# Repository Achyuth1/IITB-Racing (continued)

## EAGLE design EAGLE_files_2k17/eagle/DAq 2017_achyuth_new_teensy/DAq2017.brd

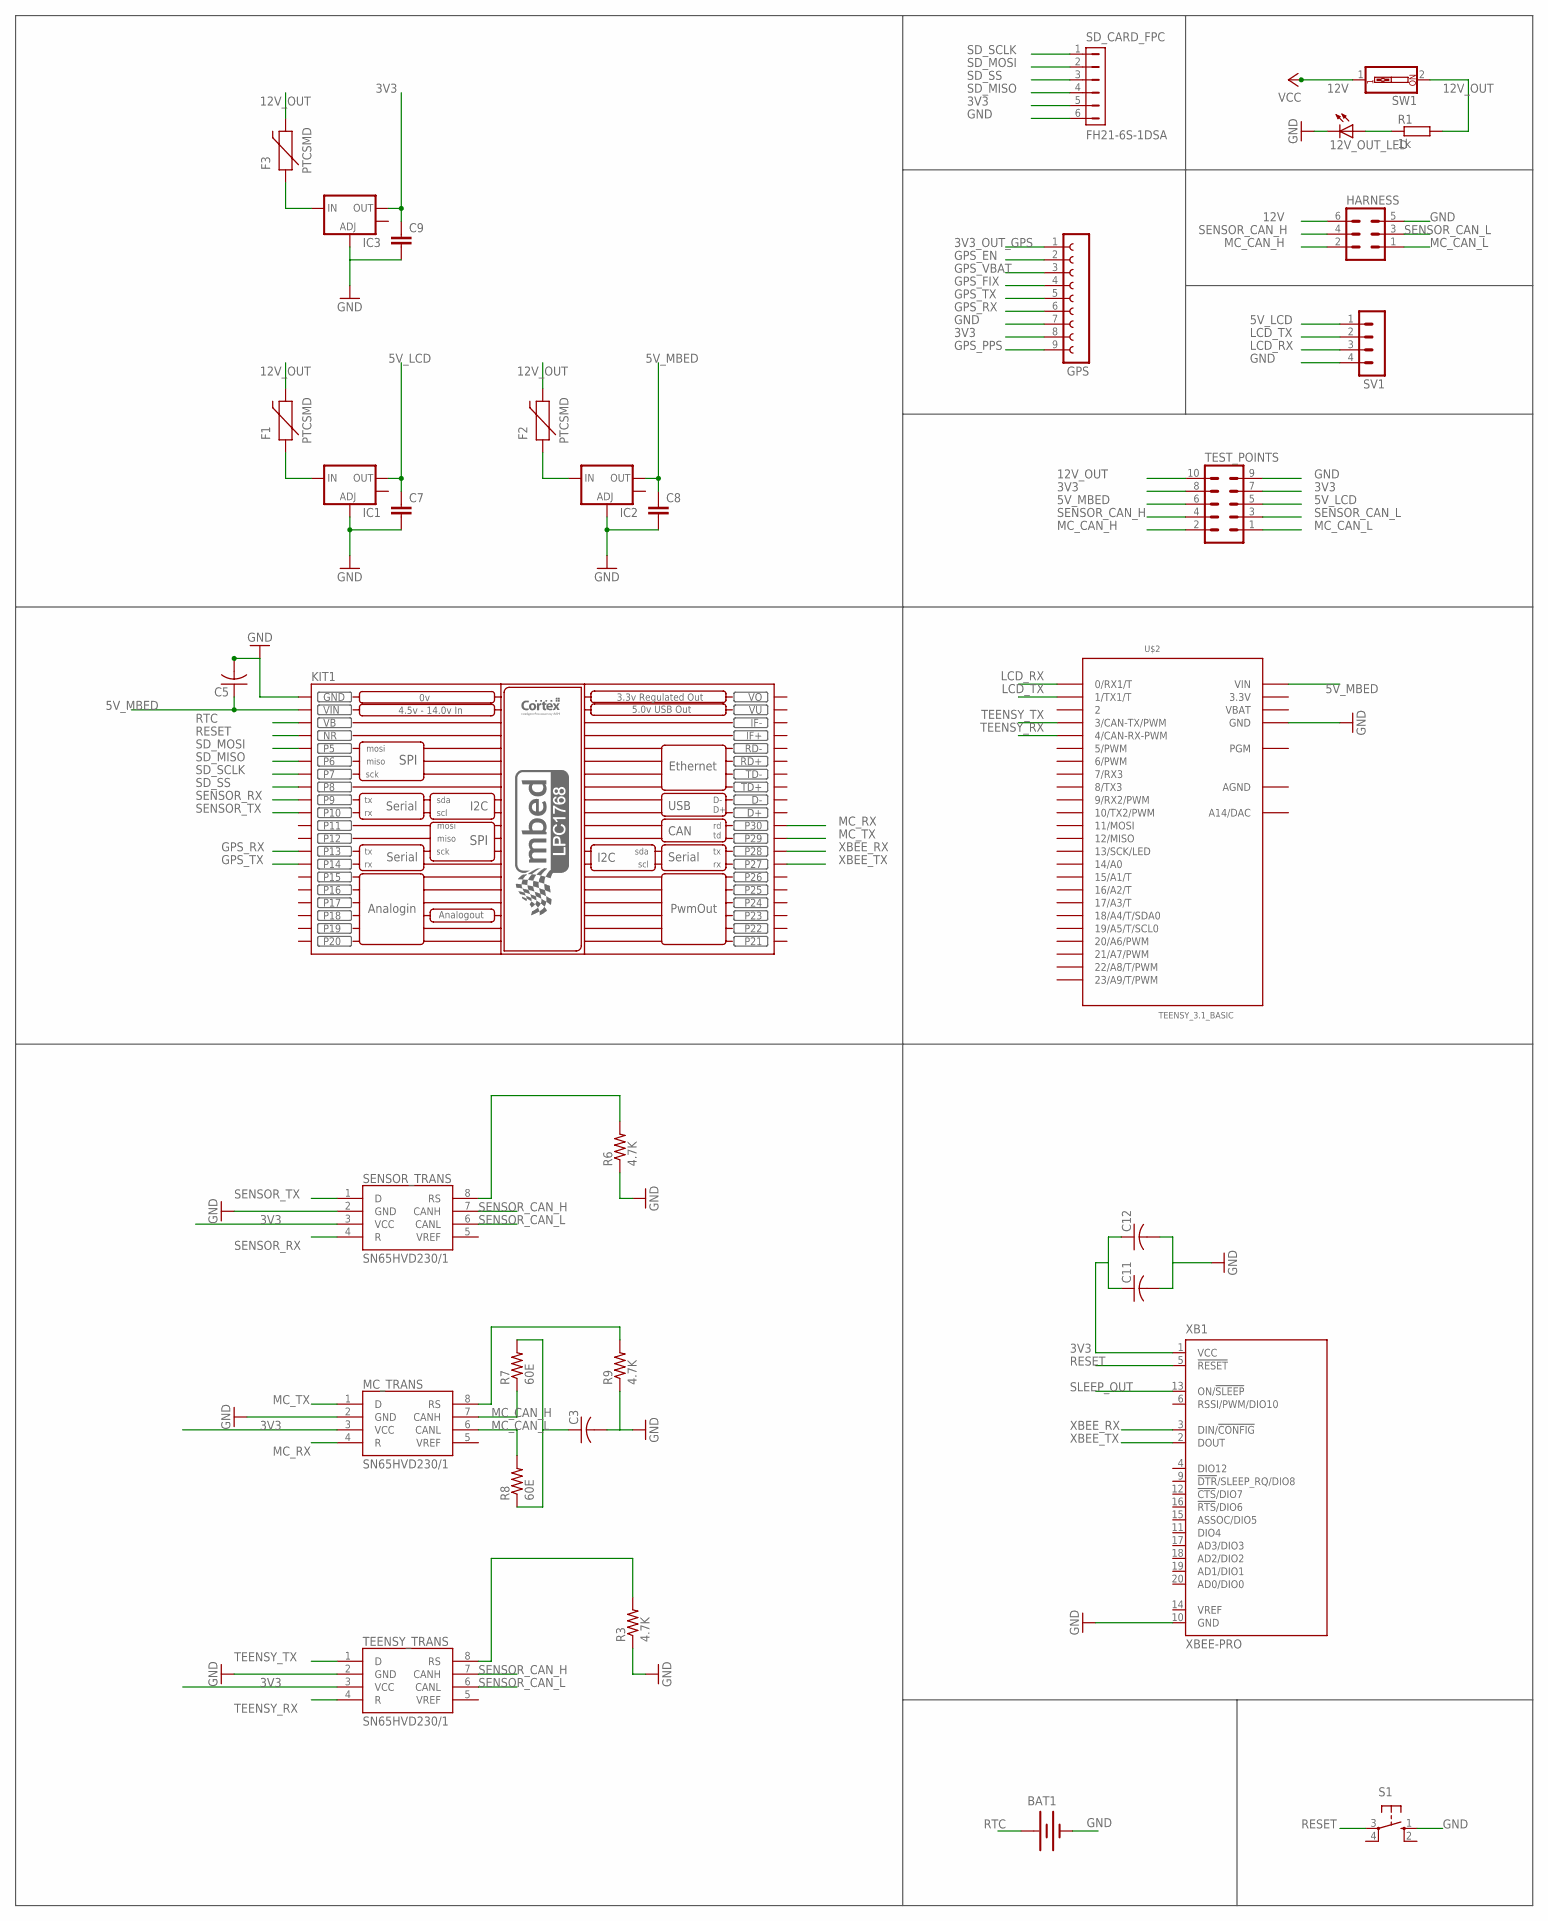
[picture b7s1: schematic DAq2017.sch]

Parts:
12V_OUT_LED: LEDCHIPLED_1206; CHIPLED_1206
BAT1: BATTERY20PTH; BATTCOM_20MM_PTH
C3, C5, C11, C12: C-USC0805; C0805
C7, C8, C9: C-EUC0805; C0805
F1, F2, F3: PTCSMD; PTC-1206
GPS: FE09-1; FE09
HARNESS: MA03-2
IC1, IC2, IC3: V_REG_LM1117SOT223; SOT223
KIT1: MBED_NXP_LPC1768; MBED-KIT
MC_TRANS: SN65HVD230/1; SO8
R1: 1k; R0805
R3, R6, R9: 4.7K; R0805
R7, R8: 60E; R0805
S1: 10-XX; B3F-10XX
SD_CARD_FPC: FH21-6S-1DSA
SENSOR_TRANS: SN65HVD230/1; SO8
SV1: MA04-1
SW1: SW_DIP-1; EDG-01
TEENSY_TRANS: SN65HVD230/1; SO8
TEST_POINTS: MA05-2
U$2: TEENSY_3.1_BASIC
XB1: XBEE-PRO

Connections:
3.3V: U$2.3.3V, U$2.3.3V1 (3.3V)
3V3: C9.1, C11.1, C12.1, GPS.8, IC3.2 (OUT), MC_TRANS.3 (VCC), SD_CARD_FPC.5, SENSOR_TRANS.3 (VCC), TEENSY_TRANS.3 (VCC), TEST_POINTS.7, TEST_POINTS.8, XB1.1 (VCC)
3V3_OUT_GPS: GPS.1
5V_LCD: C7.1, IC1.2 (OUT), SV1.1, TEST_POINTS.5
5V_MBED: C5.1, C8.1, IC2.2 (OUT), KIT1.VIN, TEST_POINTS.6, U$2.VIN
12V: HARNESS.6, SW1.1
12V_OUT: F1.2, F2.2, F3.2, R1.2, SW1.2, TEST_POINTS.10
AGND: U$2.AGND
GND: 12V_OUT_LED.C, BAT1.2 (-), C3.2, C5.2, C7.2, C8.2, C9.2, C11.2, C12.2, GPS.7, HARNESS.5, IC1.1 (ADJ), IC2.1 (ADJ), IC3.1 (ADJ), KIT1.GND, MC_TRANS.2 (GND), R3.1, R6.1, R9.1, S1.1 (S), SD_CARD_FPC.6, SENSOR_TRANS.2 (GND), SV1.4, TEENSY_TRANS.2 (GND), TEST_POINTS.9, U$2.GND, U$2.GND1 (GND), XB1.10 (GND)
GPS_EN: GPS.2
GPS_FIX: GPS.4
GPS_PPS: GPS.9
GPS_RX: GPS.6, KIT1.P$13 (P13)
GPS_TX: GPS.5, KIT1.P$14 (P14)
GPS_VBAT: GPS.3
LCD_RX: SV1.3, U$2.0 (0/RX1/T)
LCD_TX: SV1.2, U$2.1 (1/TX1/T)
MC_CAN_H: HARNESS.2, MC_TRANS.7 (CANH), R7.1, TEST_POINTS.2
MC_CAN_L: HARNESS.1, MC_TRANS.6 (CANL), R8.2, TEST_POINTS.1
MC_RX: KIT1.P$30 (P30), MC_TRANS.4 (R)
MC_TX: KIT1.P$29 (P29), MC_TRANS.1 (D)
unnamed: R3.2, TEENSY_TRANS.8 (RS)
unnamed: 12V_OUT_LED.A, R1.1
unnamed: R6.2, SENSOR_TRANS.8 (RS)
unnamed: C3.1, R7.2, R8.1
unnamed: MC_TRANS.8 (RS), R9.2
unnamed: F1.1, IC1.3 (IN)
unnamed: F2.1, IC2.3 (IN)
unnamed: F3.1, IC3.3 (IN)
RESET: KIT1.NR, S1.3, XB1.5 (!RESET)
RTC: BAT1.1 (+), KIT1.VB
SD_MISO: KIT1.P$6 (P6), SD_CARD_FPC.4
SD_MOSI: KIT1.P$5 (P5), SD_CARD_FPC.2
SD_SCLK: KIT1.P$7 (P7), SD_CARD_FPC.1
SD_SS: KIT1.P$8 (P8), SD_CARD_FPC.3
SENSOR_CAN_H: HARNESS.4, SENSOR_TRANS.7 (CANH), TEENSY_TRANS.7 (CANH), TEST_POINTS.4
SENSOR_CAN_L: HARNESS.3, SENSOR_TRANS.6 (CANL), TEENSY_TRANS.6 (CANL), TEST_POINTS.3
SENSOR_RX: KIT1.P$9 (P9), SENSOR_TRANS.4 (R)
SENSOR_TX: KIT1.P$10 (P10), SENSOR_TRANS.1 (D)
SLEEP_OUT: XB1.13 (ON/!SLEEP)
TEENSY_RX: TEENSY_TRANS.4 (R), U$2.4 (4/CAN-RX-PWM)
TEENSY_TX: TEENSY_TRANS.1 (D), U$2.3 (3/CAN-TX/PWM)
VBAT: U$2.VBAT
VO: KIT1.VOUT (VO)
VU: KIT1.VU
XBEE_RX: KIT1.P$28 (P28), XB1.3 (DIN/!CONFIG)
XBEE_TX: KIT1.P$27 (P27), XB1.2 (DOUT)

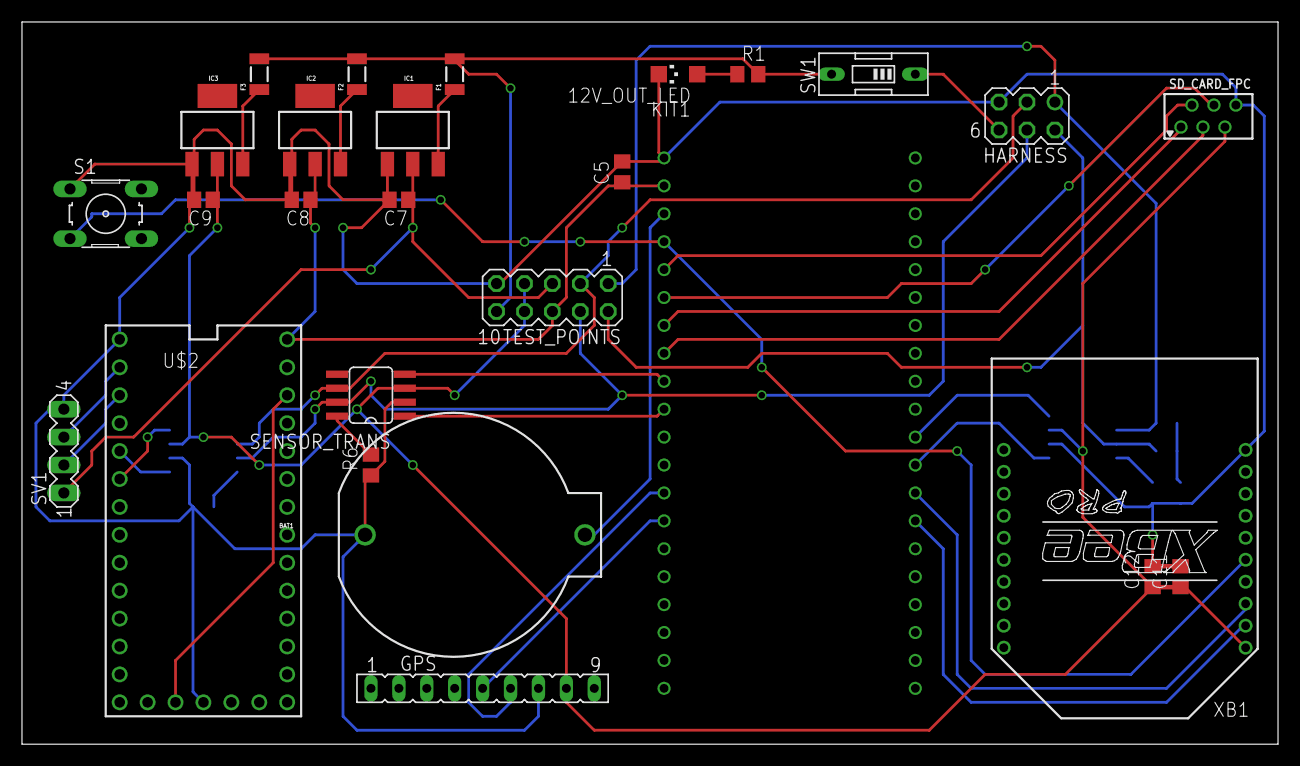
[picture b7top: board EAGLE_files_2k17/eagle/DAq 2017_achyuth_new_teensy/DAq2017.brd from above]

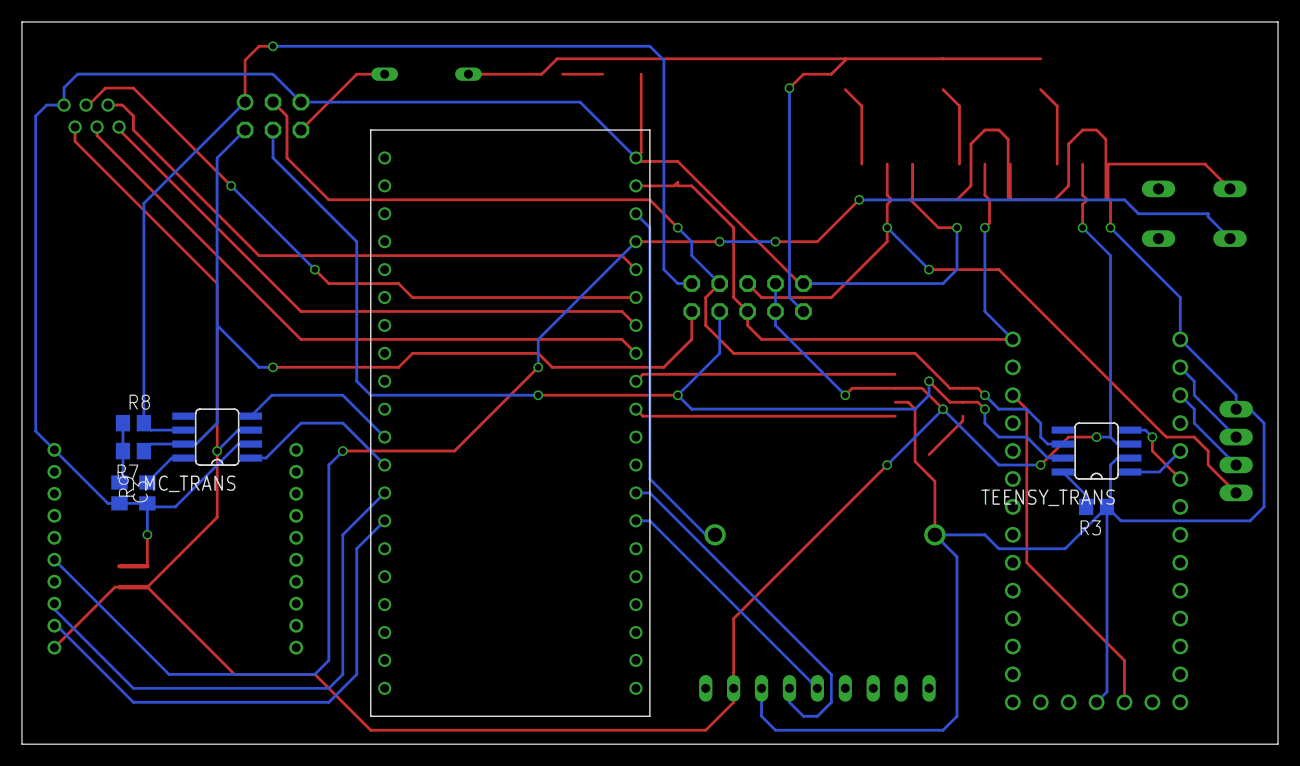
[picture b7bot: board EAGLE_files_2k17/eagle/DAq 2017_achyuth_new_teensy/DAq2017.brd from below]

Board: 2 copper layers, 114.3 x 65.7 mm, 34 parts (7 on the bottom side), 37 nets.

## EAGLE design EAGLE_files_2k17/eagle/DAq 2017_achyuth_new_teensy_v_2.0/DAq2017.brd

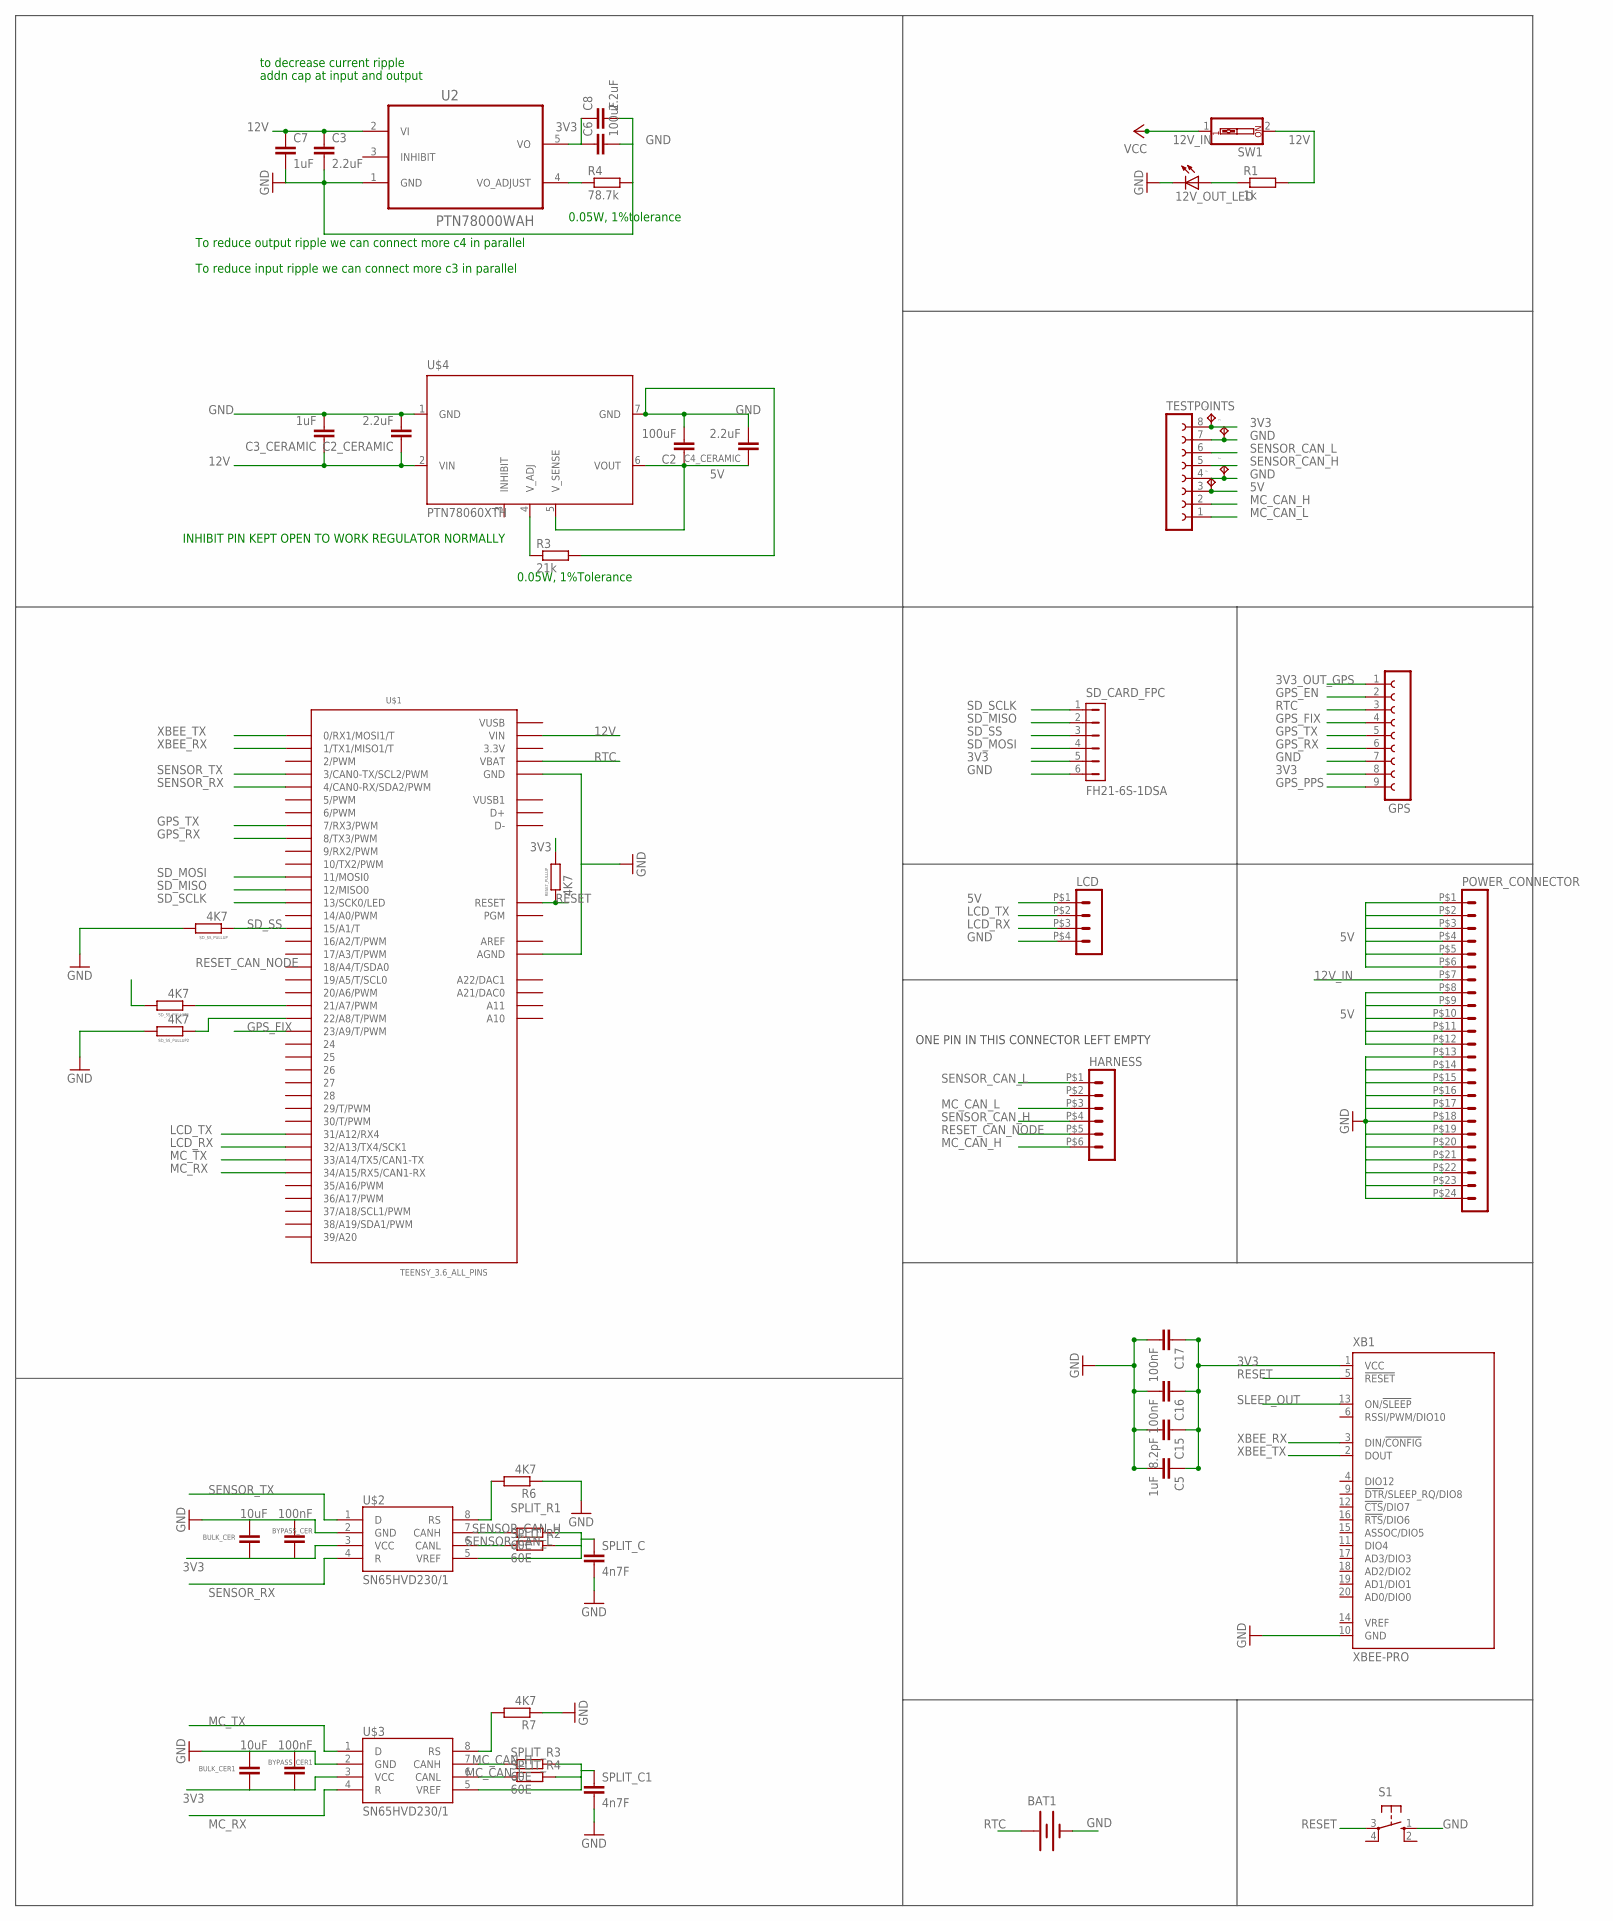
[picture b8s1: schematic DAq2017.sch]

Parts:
12V_OUT_LED: LEDCHIPLED_1206; CHIPLED_1206
BAT1: BATTERY20PTH; BATTCOM_20MM_PTH
BULK_CER, BULK_CER1: 10uF; C0805
BYPASS_CER, BYPASS_CER1: 100nF; C0805
C2, C6: 100uF; C0805
C2_CERAMIC, C3, C4_CERAMIC, C8: 2.2uF; C0805
C3_CERAMIC, C5, C7: 1uF; C0805
C15: 8.2pF; C0805
C16, C17: 100nF; C0805
GPS: FE09-1; FE09
HARNESS: HEADER_POS6_43045-0612; 43045-0612
LCD: HEADER_POS4_43045-0412; 43045-0412
POWER_CONNECTOR: HEADER_POS24_43045-2412; 43045-2412
R1: 1k; R0805
R3: 21k; R0805
R4: 78.7k; R0805
R6, R7: 4K7; R0805
RESET_PULLUP: 4K7; R0805
S1: 10-XX; B3F-10XX
SD_CARD_FPC: FH21-6S-1DSA
SD_SS_PULLUP, SD_SS_PULLUP1, SD_SS_PULLUP2: 4K7; R0805
SPLIT_C, SPLIT_C1: 4n7F; C0805
SPLIT_R1, SPLIT_R2, SPLIT_R3, SPLIT_R4: 60E; R0805
SW1: SW_DIP-1; EDG-01
TESTPOINTS: FE08-1; FE08
TP2, TP3, TP4, TP5: TPPAD1-17Y; P1-17Y
U2: PTN78000WAH; TI_PTN78000WAH
U$1: TEENSY_3.6_ALL_PINS
U$2, U$3: SN65HVD230/1; SO8
U$4: PTN78060XTH; PTN78060X_TH
XB1: XBEE-PRO

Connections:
3.3V: U$1.3.3V, U$1.3.3V3 (3.3V), U$1.3.3V4 (3.3V)
3V3: BULK_CER.1, BULK_CER1.1, BYPASS_CER.1, BYPASS_CER1.1, C5.1, C6.1, C8.1, C15.1, C16.1, C17.1, GPS.8, RESET_PULLUP.2, SD_CARD_FPC.5, SD_SS_PULLUP1.2, TESTPOINTS.8, TP2.TP, U2.5 (VO), U$2.3 (VCC), U$3.3 (VCC), XB1.1 (VCC)
3V3_OUT_GPS: GPS.1
5V: C2.1, C4_CERAMIC.1, LCD.P$1 (1), POWER_CONNECTOR.P$1 (1), POWER_CONNECTOR.P$2 (2), POWER_CONNECTOR.P$3 (3), POWER_CONNECTOR.P$4 (4), POWER_CONNECTOR.P$5 (5), POWER_CONNECTOR.P$6 (6), POWER_CONNECTOR.P$8 (8), POWER_CONNECTOR.P$9 (9), POWER_CONNECTOR.P$10 (10), POWER_CONNECTOR.P$11 (11), POWER_CONNECTOR.P$12 (12), TESTPOINTS.3, TP5.TP, U$4.5 (V_SENSE), U$4.6 (VOUT)
12V: C2_CERAMIC.1, C3.1, C3_CERAMIC.1, C7.1, R1.2, SW1.2, U2.2 (VI), U$1.VIN, U$4.2 (VIN)
12V_IN: POWER_CONNECTOR.P$7 (7), SW1.1
AREF: U$1.AREF
GND: 12V_OUT_LED.C, BAT1.2 (-), BULK_CER.2, BULK_CER1.2, BYPASS_CER.2, BYPASS_CER1.2, C2.2, C2_CERAMIC.2, C3.2, C3_CERAMIC.2, C4_CERAMIC.2, C5.2, C6.2, C7.2, C8.2, C15.2, C16.2, C17.2, GPS.7, LCD.P$4 (4), POWER_CONNECTOR.P$13 (13), POWER_CONNECTOR.P$14 (14), POWER_CONNECTOR.P$15 (15), POWER_CONNECTOR.P$16 (16), POWER_CONNECTOR.P$17 (17), POWER_CONNECTOR.P$18 (18), POWER_CONNECTOR.P$19 (19), POWER_CONNECTOR.P$20 (20), POWER_CONNECTOR.P$21 (21), POWER_CONNECTOR.P$22 (22), POWER_CONNECTOR.P$23 (23), POWER_CONNECTOR.P$24 (24), R3.2, R4.2, R6.1, R7.1, S1.1 (S), SD_CARD_FPC.6, SD_SS_PULLUP.2, SD_SS_PULLUP2.2, SPLIT_C.2, SPLIT_C1.2, TESTPOINTS.4, TESTPOINTS.7, TP3.TP, TP4.TP, U2.1 (GND), U$1.AGND, U$1.GND, U$1.GND1 (GND), U$1.GND3 (GND), U$1.GND4 (GND), U$1.GND6 (GND), U$2.2 (GND), U$3.2 (GND), U$4.1 (GND), U$4.7 (GND), XB1.10 (GND)
GPS_EN: GPS.2
GPS_FIX: GPS.4, U$1.23/A9 (23/A9/T/PWM)
GPS_PPS: GPS.9
GPS_RX: GPS.6, U$1.8 (8/TX3/PWM)
GPS_TX: GPS.5, U$1.7 (7/RX3/PWM)
LCD_RX: LCD.P$3 (3), U$1.32/A13 (32/A13/TX4/SCK1)
LCD_TX: LCD.P$2 (2), U$1.31/A12 (31/A12/RX4)
LULZ: R6.2, U$2.8 (RS)
MC_CAN_H: HARNESS.P$6 (6), SPLIT_R3.1, TESTPOINTS.2, U$3.7 (CANH)
MC_CAN_L: HARNESS.P$3 (3), SPLIT_R4.1, TESTPOINTS.1, U$3.6 (CANL)
MC_RX: U$1.34/A15 (34/A15/RX5/CAN1-RX), U$3.4 (R)
MC_TX: U$1.33/A14 (33/A14/TX5/CAN1-TX), U$3.1 (D)
unnamed: SD_SS_PULLUP2.1, U$1.22/A8 (22/A8/T/PWM)
unnamed: R3.1, U$4.4 (V_ADJ)
unnamed: R4.1, U2.4 (VO_ADJUST)
unnamed: 12V_OUT_LED.A, R1.1
unnamed: R7.2, U$3.8 (RS)
unnamed: SPLIT_C1.1, SPLIT_R3.2, SPLIT_R4.2, U$3.5 (VREF)
unnamed: SPLIT_C.1, SPLIT_R1.2, SPLIT_R2.2, U$2.5 (VREF)
RESET: RESET_PULLUP.1, S1.3, U$1.RESET, XB1.5 (!RESET)
RESET_CAN_NODE: HARNESS.P$5 (5), SD_SS_PULLUP1.1, U$1.21/A7 (21/A7/PWM)
RTC: BAT1.1 (+), GPS.3, U$1.VBAT
SD_MISO: SD_CARD_FPC.2, U$1.12 (12/MISO0)
SD_MOSI: SD_CARD_FPC.4, U$1.11 (11/MOSI0)
SD_SCLK: SD_CARD_FPC.1, U$1.13 (13/SCK0/LED)
SD_SS: SD_CARD_FPC.3, SD_SS_PULLUP.1, U$1.15/A1 (15/A1/T)
SENSOR_CAN_H: HARNESS.P$4 (4), SPLIT_R1.1, TESTPOINTS.5, U$2.7 (CANH)
SENSOR_CAN_L: HARNESS.P$1 (1), SPLIT_R2.1, TESTPOINTS.6, U$2.6 (CANL)
SENSOR_RX: U$1.4 (4/CAN0-RX/SDA2/PWM), U$2.4 (R)
SENSOR_TX: U$1.3 (3/CAN0-TX/SCL2/PWM), U$2.1 (D)
SLEEP_OUT: XB1.13 (ON/!SLEEP)
VUSB: U$1.VUSB
VUSB1: U$1.VUSB1
XBEE_RX: U$1.1 (1/TX1/MISO1/T), XB1.3 (DIN/!CONFIG)
XBEE_TX: U$1.0 (0/RX1/MOSI1/T), XB1.2 (DOUT)

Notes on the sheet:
0.05W, 1%Tolerance
INHIBIT PIN KEPT OPEN TO WORK REGULATOR NORMALLY
To reduce output ripple we can connect more c4 in parallel
To reduce input ripple we can connect more c3 in parallel
0.05W, 1%tolerance
to decrease current ripple
addn cap at input and output
ONE PIN IN THIS CONNECTOR LEFT EMPTY

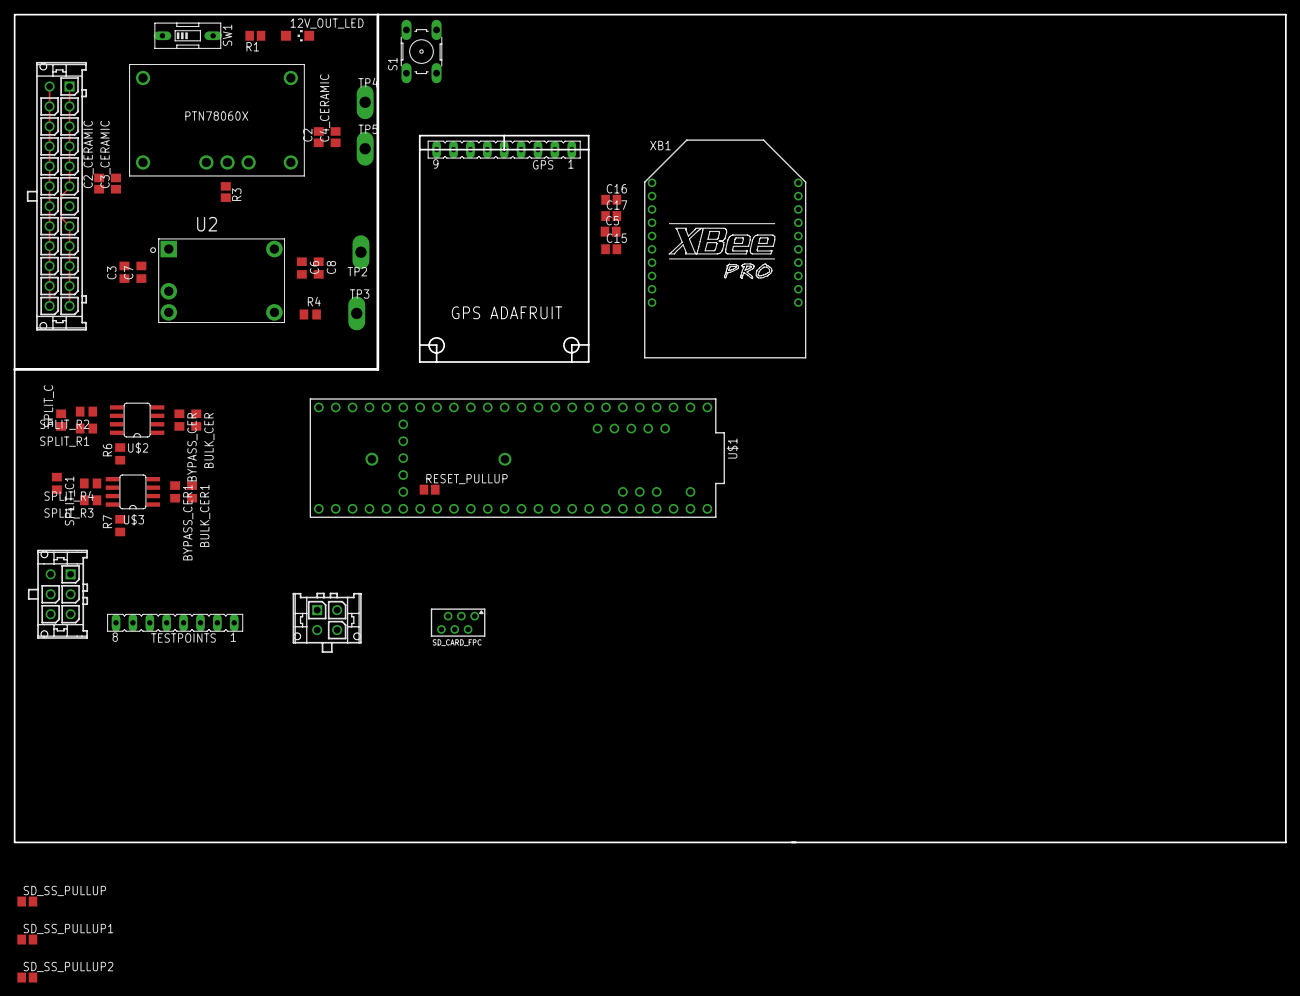
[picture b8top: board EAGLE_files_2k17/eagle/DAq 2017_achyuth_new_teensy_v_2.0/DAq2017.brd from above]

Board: 2 copper layers, 191.1 x 124.5 mm, 51 parts (1 on the bottom side), 36 nets.

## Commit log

2017-03-16 Konda craxx
2017-03-29 RPM node teensy code without can added
2017-03-29 All eagle files added ..DAq board will be updated soon
2017-04-04 Daq done; CAN ANalog has to be edited; RPM node also remains
2017-04-05 Analog node done bitches :D, RPM will be done in 2 hrs :D #peace
2017-04-06 All boards except SD Card is donegit add . will buy SD Card :D #peace
2017-04-24 Final boards in daqcanboards
